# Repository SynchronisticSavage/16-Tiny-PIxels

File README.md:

16 Tiny Pixels!

(Cause sometimes you just need a little ring of programable leds...)

A Simple little board combining an AT-Tiny, 16 WS2812 LEDS, Micro-USB Connector, 2x3 Pin Header, and a handful of capacitors, resistors, and Diodes. All Packed into a nice circular little package.

Relativly large smd components, and hand solder pads have been used to make this board simple to solder.

MicroNuculus can be programmed to the Attiny-85 prior to soldering or via the pin header, allowing subsequent programming to be done over the USB.

Code for this and controlling the ws2812 LEDs can be found somewhere out there on the interwebs(Multiple Sources), you know how to find it ;)

To keep this board as simple as possible there is no power protection cicuitry provided...this may change in later versions, but i like the simpisity for now.

As of the Time of This Writing this board has not been tested, this is the first board this being has designed

One thing i am not certain about is the capacitor placment and connection, i think it should work as it is, but maybe i am wrong?

Also not sure if it is a good idea to fill the top layer with gnd and bottom with vcc, mostly just wanted to try the filled zone feature...seems good...pretty sure it is good...let me know if i am wrong... :)

Note: this board was created using the WifI Pixels kicad files as a template, a cool Open Source Board using the esp8266 created by ProtoNeer.
Check it out here:
https://github.com/Protoneer/WifiPixels
and here:
https://wiki.protoneer.co.nz/WifiPixels

this board is also based on the Digispark Schematics Found Here:
http://www.instructables.com/id/Digispark-DIY-The-smallest-USB-Arduino/

Big Ups to the Open Source Community!
TO-DO!
Organize and rename stuff
make sure it is portable and opens fine on other systems 
make bettery PCB-Art
Add IR Sensor possibly another attiny to fully support IR (More Testing Required~!)
Add WS2812 LEDs to the 3D Viewer View :P

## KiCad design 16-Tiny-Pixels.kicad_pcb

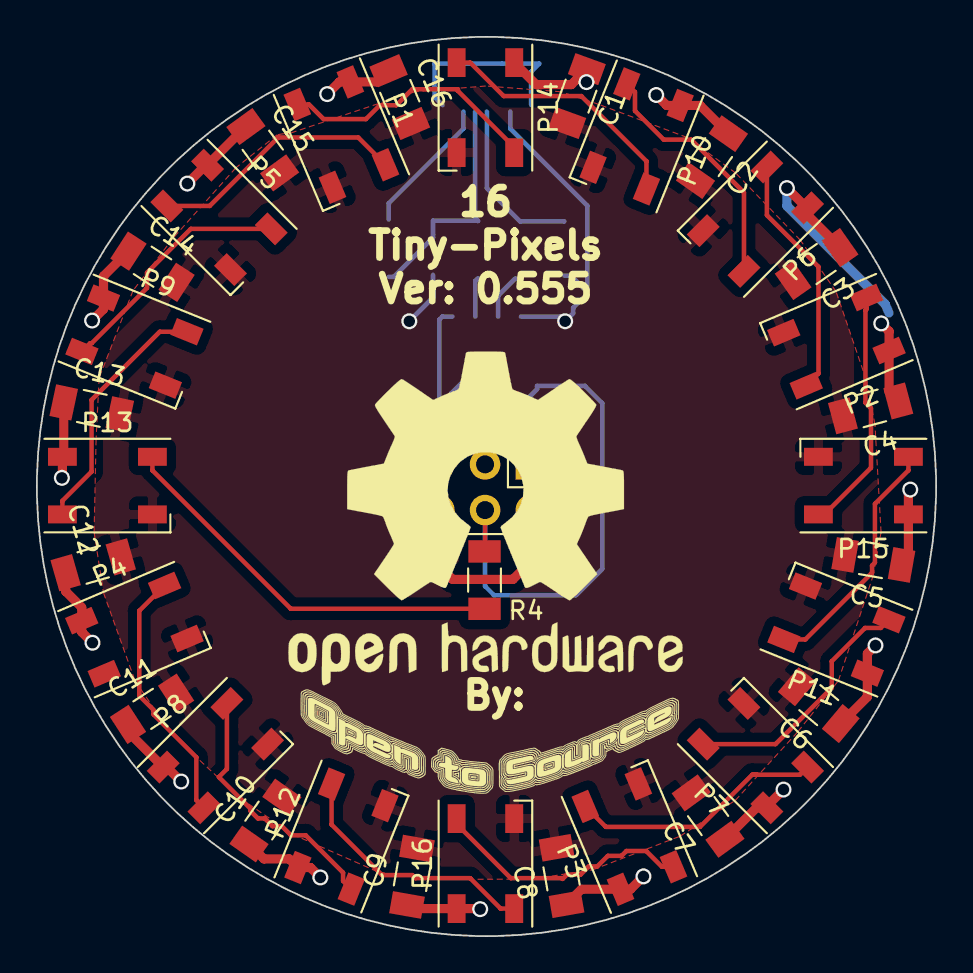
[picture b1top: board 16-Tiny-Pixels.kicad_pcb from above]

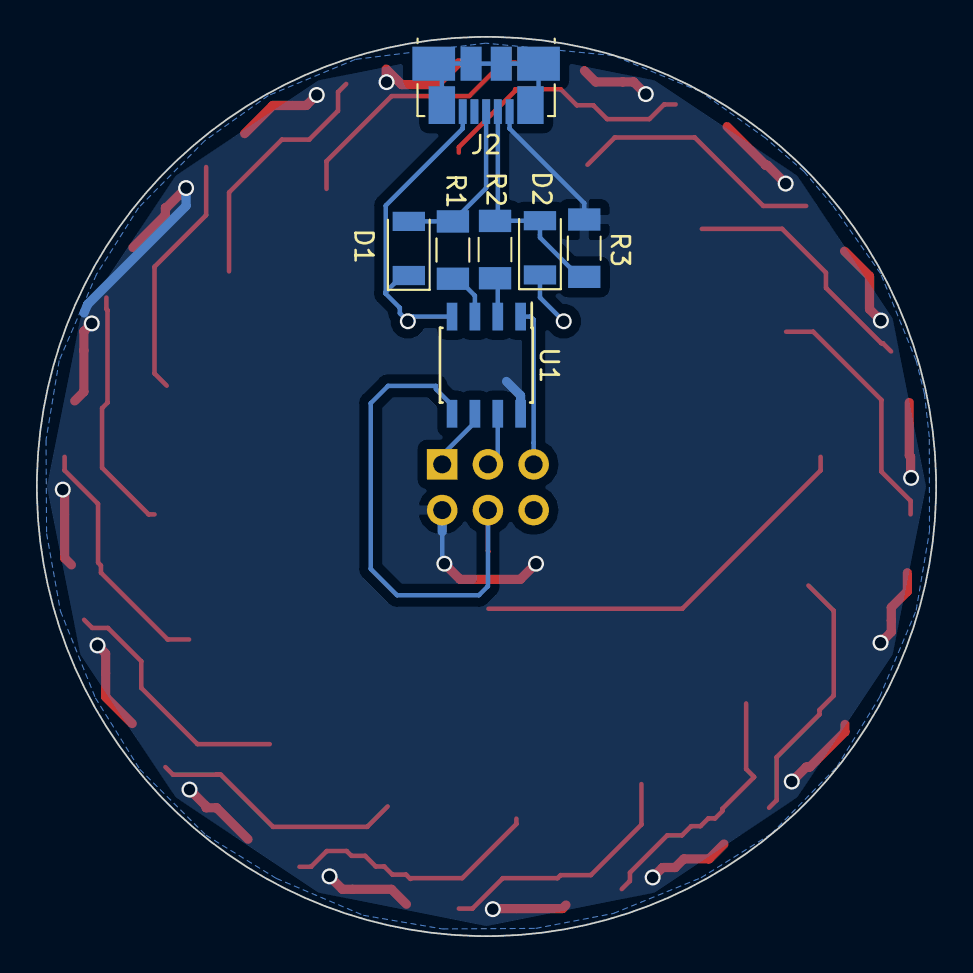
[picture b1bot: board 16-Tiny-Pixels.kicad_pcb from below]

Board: 2 copper layers, 50.0 x 50.0 mm, 41 parts (7 on the bottom side), 26 nets.

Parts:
C1: 0.1uf; C_1206_3216Metric_Pad1.24x1.80mm_HandSolder
C2, C3, C4, C5, C6, C7, C8, C9, C10, C11, C12, C13, C14, C15, C16: C; C_1206_3216Metric_Pad1.24x1.80mm_HandSolder
D1, D2: 3.6V; D_1206_3216Metric_Pad1.07x1.80mm_HandSolder
J1: ICSP; PinHeader_2x03_P2.54mm_Vertical
J2: USB_B_Micro; USB_Micro-B_Molex_47346-0001
P1, P2, P3, P4, P5, P6, P7, P8, P9, P10, P11, P12, P13, P14, P15, P16: WS2812B; LED_WS2812B-PLCC4
R1, R2: 68; R_1206_3216Metric_Pad1.24x1.80mm_HandSolder
R3: 1.5K; R_1206_3216Metric_Pad1.24x1.80mm_HandSolder
R4: 500; R_1206_3216Metric_Pad1.24x1.80mm_HandSolder
U1: ATTINY85-20SU; SOIC-8_3.9x4.9mm_P1.27mm

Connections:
Data-IN: J1.4, R4.2, U1.5
GND: C1.2, C2.2, C3.2, C4.2, C5.2, C6.2, C7.2, C8.2, C9.2, C10.2, C11.2, C12.2, C13.2, C14.2, C15.2, C16.2, D1.1, D2.1, J1.6, J2.5, P1.3, P2.3, P3.3, P4.3, P5.3, P6.3, P7.3, P8.3, P9.3, P10.3, P11.3, P12.3, P13.3, P14.3, P15.3, P16.3, U1.4
unnamed: D1.2, J2.3, R1.2
unnamed: D2.2, J2.2, R2.2, R3.1
unnamed: J1.1, U1.6
unnamed: J1.3, U1.7
unnamed: J1.5, U1.1
unnamed: P1.2, P14.4
unnamed: P1.4, P5.2
unnamed: P2.4, P6.2
unnamed: P3.4, P7.2
unnamed: P4.4, P8.2
unnamed: P5.4, P9.2
unnamed: P6.4, P10.2
unnamed: P10.4, P14.2
unnamed: P7.4, P11.2
unnamed: P11.4, P15.2
unnamed: P8.4, P12.2
unnamed: P12.4, P16.2
unnamed: P9.4, P13.2
unnamed: P13.4, R4.1
unnamed: P2.2, P15.4
unnamed: P3.2, P16.4
unnamed: R1.1, U1.3
unnamed: R2.1, U1.2
VCC: C1.1, C2.1, C3.1, C4.1, C5.1, C6.1, C7.1, C8.1, C9.1, C10.1, C11.1, C12.1, C13.1, C14.1, C15.1, C16.1, J1.2, J2.1, P1.1, P2.1, P3.1, P4.1, P5.1, P6.1, P7.1, P8.1, P9.1, P10.1, P11.1, P12.1, P13.1, P14.1, P15.1, P16.1, R3.2, U1.8

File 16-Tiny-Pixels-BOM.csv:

"Id";"Designator";"Package";"Quantity";"Designation";"Supplier and ref";
1;"G***";"OTS-Logo-Warp-Neon-22.5mm-fit";1;"LOGO";;;
2;"C1";"C_1206_3216Metric_Pad1.24x1.80mm_HandSolder";1;"0.1uf";;;
3;"C2,C3,C4,C5,C6,C7,C8,C9,C10,C11,C12,C13,C14,C15,C16";"C_1206_3216Metric_Pad1.24x1.80mm_HandSolder";15;"C";;;
4;"D1,D2";"D_1206_3216Metric_Pad1.07x1.80mm_HandSolder";2;"3.6V";;;
5;"J1";"PinHeader_2x03_P2.54mm_Vertical";1;"ICSP";;;
6;"R1,R2";"R_1206_3216Metric_Pad1.24x1.80mm_HandSolder";2;"68";;;
7;"R3";"R_1206_3216Metric_Pad1.24x1.80mm_HandSolder";1;"1.5K";;;
8;"R4";"R_1206_3216Metric_Pad1.24x1.80mm_HandSolder";1;"500";;;
9;"U1";"SOIC-8_3.9x4.9mm_P1.27mm";1;"ATTINY85-20SU";;;
10;"P1,P2,P3,P4,P5,P6,P7,P8,P9,P10,P11,P12,P13,P14,P15,P16";"LED_WS2812B-PLCC4";16;"WS2812B";;;
11;"J2";"USB_Micro-B_Molex_47346-0001";1;"USB_B_Micro";;;
12;"REF**";"OSHW-Logo2_24.3x20mm_SilkScreen";1;"OSHW-Logo2_24.3x20mm_SilkScreen";;;

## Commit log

2018-02-25 16-Tiny-Pixels Enter the World.
2018-02-25 Added Picture of 3D View
2018-02-25 Updated Readme to Include Picture of 3D View
